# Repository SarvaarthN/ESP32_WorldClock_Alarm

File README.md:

# 12 Hr Clock

This project is a **Digital Logic Design (Sem 3) course project at VJTI**, focused on the design and implementation of a non-microcontroller-based digital clock using fundamental digital electronics components.

A **crystal oscillator** is employed to generate a stable and accurate clock signal, which is then divided and processed using a series of decade counters to achieve precise timekeeping.

The clock is configured to operate in a 12-hour format, incorporating appropriate rollover logic for hours. **Seven-segment display driver ICs** are used to interface with the displays, ensuring clear and reliable visualization of hours and minutes.

This project emphasizes a deep understanding of frequency division, time counting, sequential logic, and display interfacing, demonstrating accurate timekeeping without relying on microcontrollers or firmware, and instead leveraging core digital logic design principles.

## Folder Structure
- **Docs** – Documentation, reports, and design references  
- **PCB** – Circuit schematics, board layout, and related design files  

```12-Hr-Clock/
├── Docs/
│   └── Datasheets/
│
├── PCB/
│   ├── 12HrClock_PCB/
│   │   ├── 12HrClock_PCB-backups/
│   │   └── v1-backups/
│   │
│   └── Gerberv3/
│
└── README.md

```

## PCB Pictures

## Contributors

- [Sarvaarth Narang](https://github.com/SarvaarthN)
- [Paarth Shirsat](https://github.com/Paarth-Shirsat)
- [Bhakti Assar](https://github.com/Bhakti-A)

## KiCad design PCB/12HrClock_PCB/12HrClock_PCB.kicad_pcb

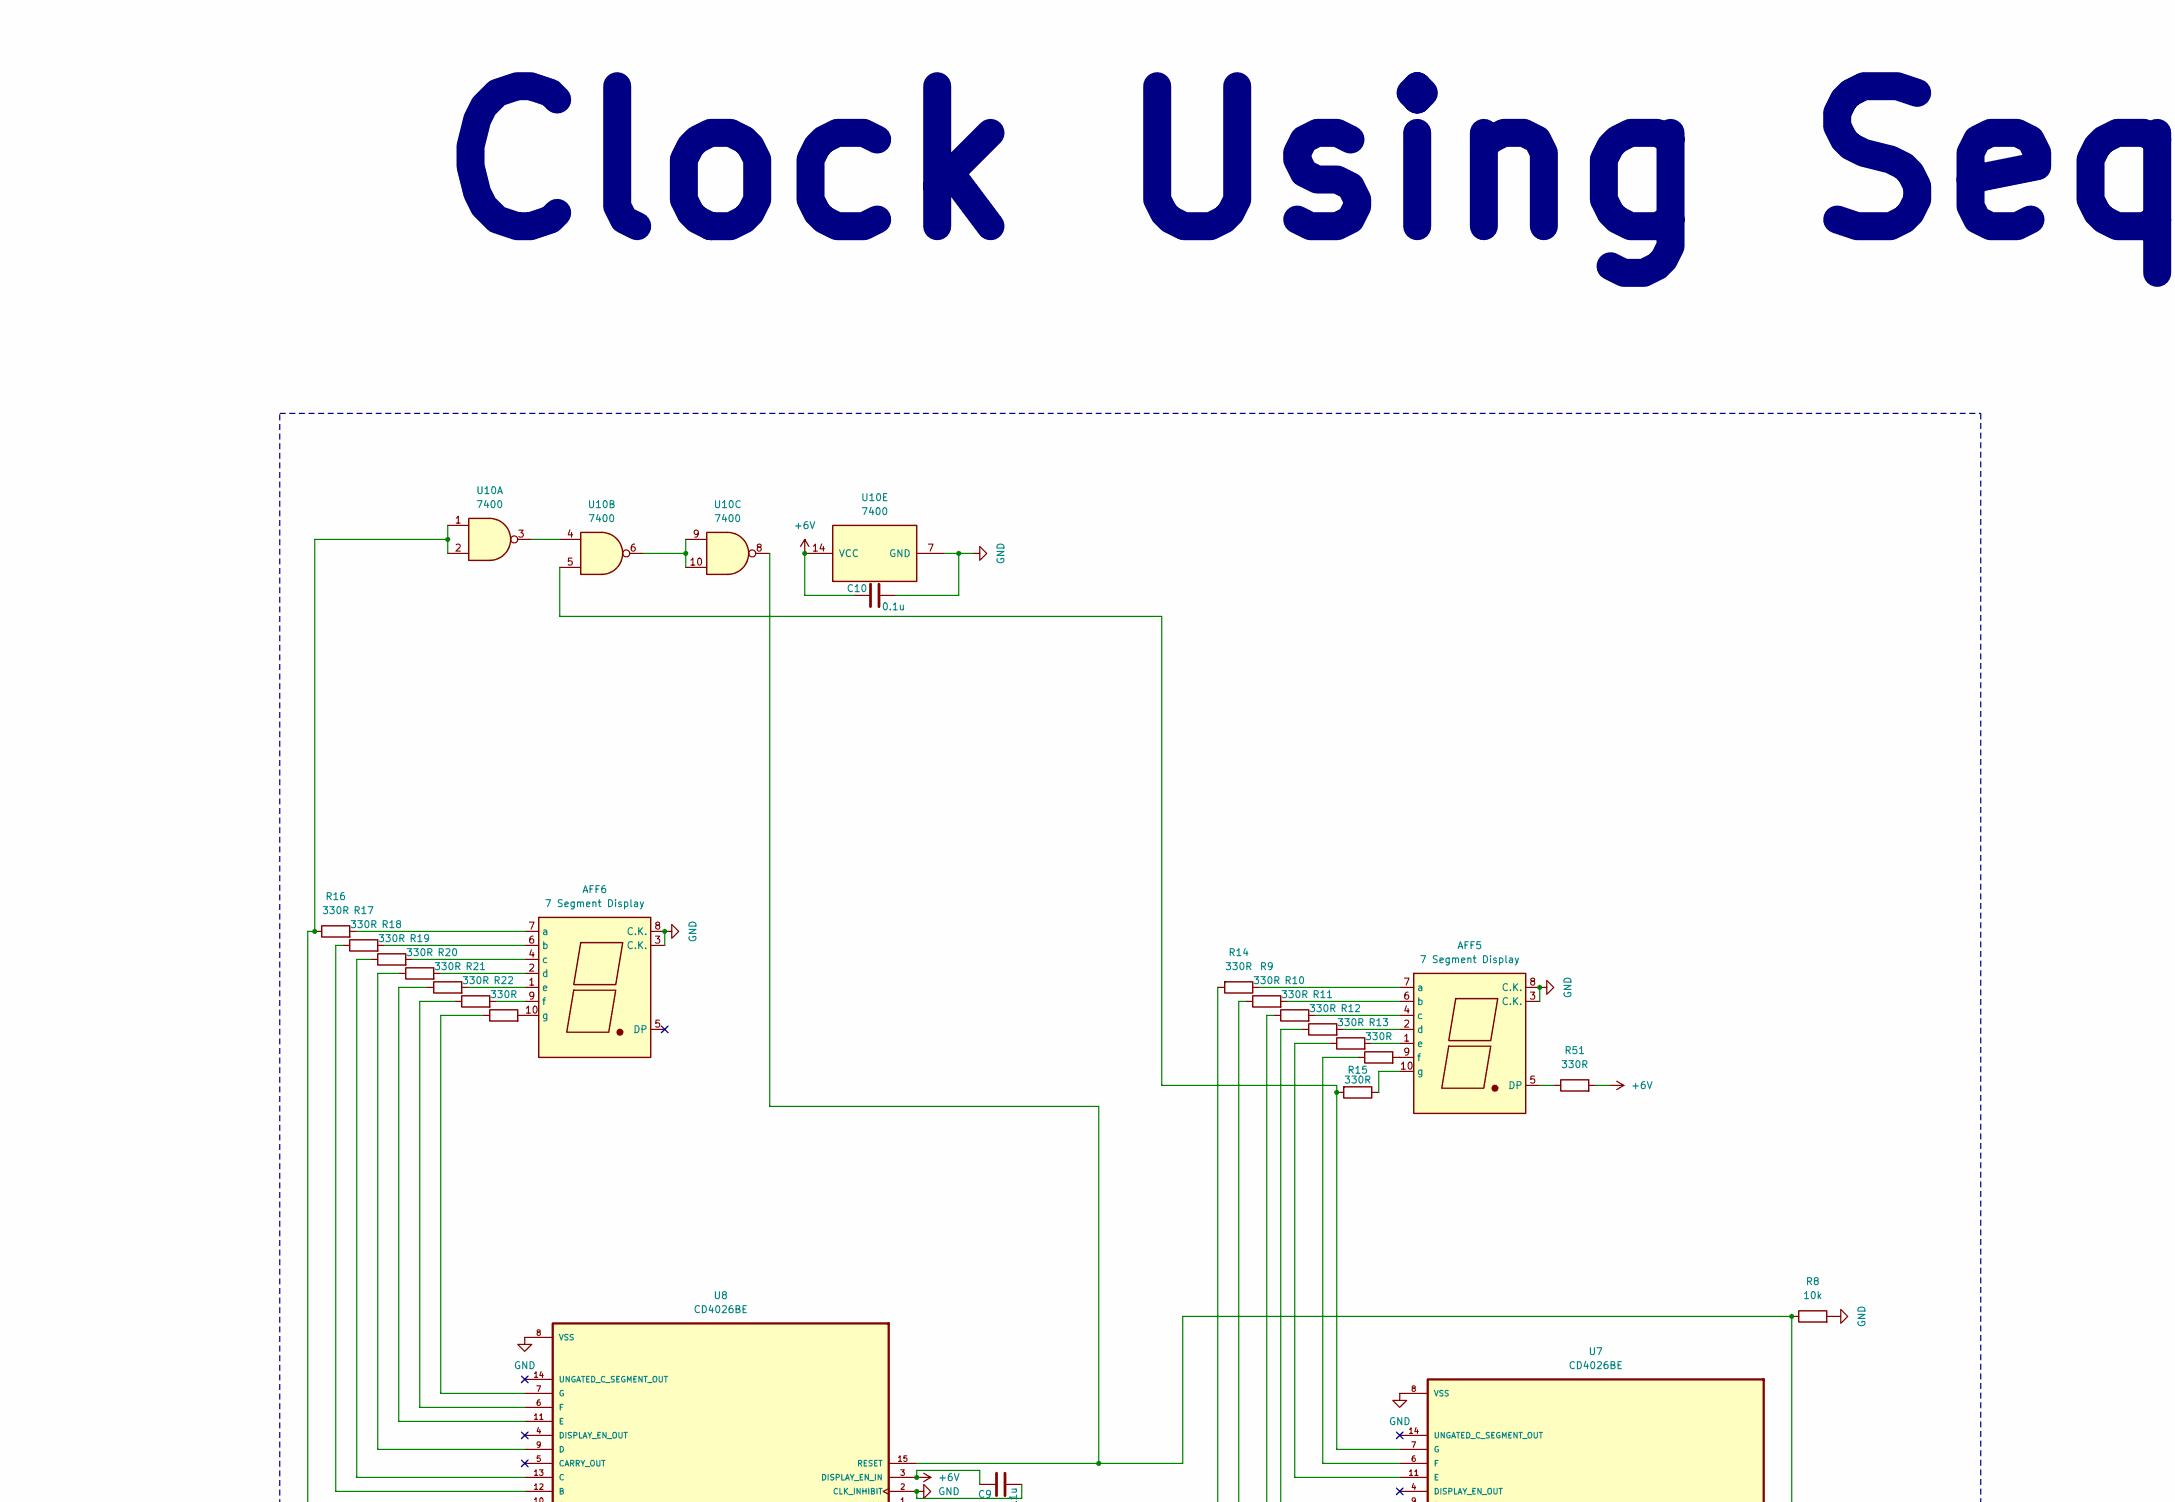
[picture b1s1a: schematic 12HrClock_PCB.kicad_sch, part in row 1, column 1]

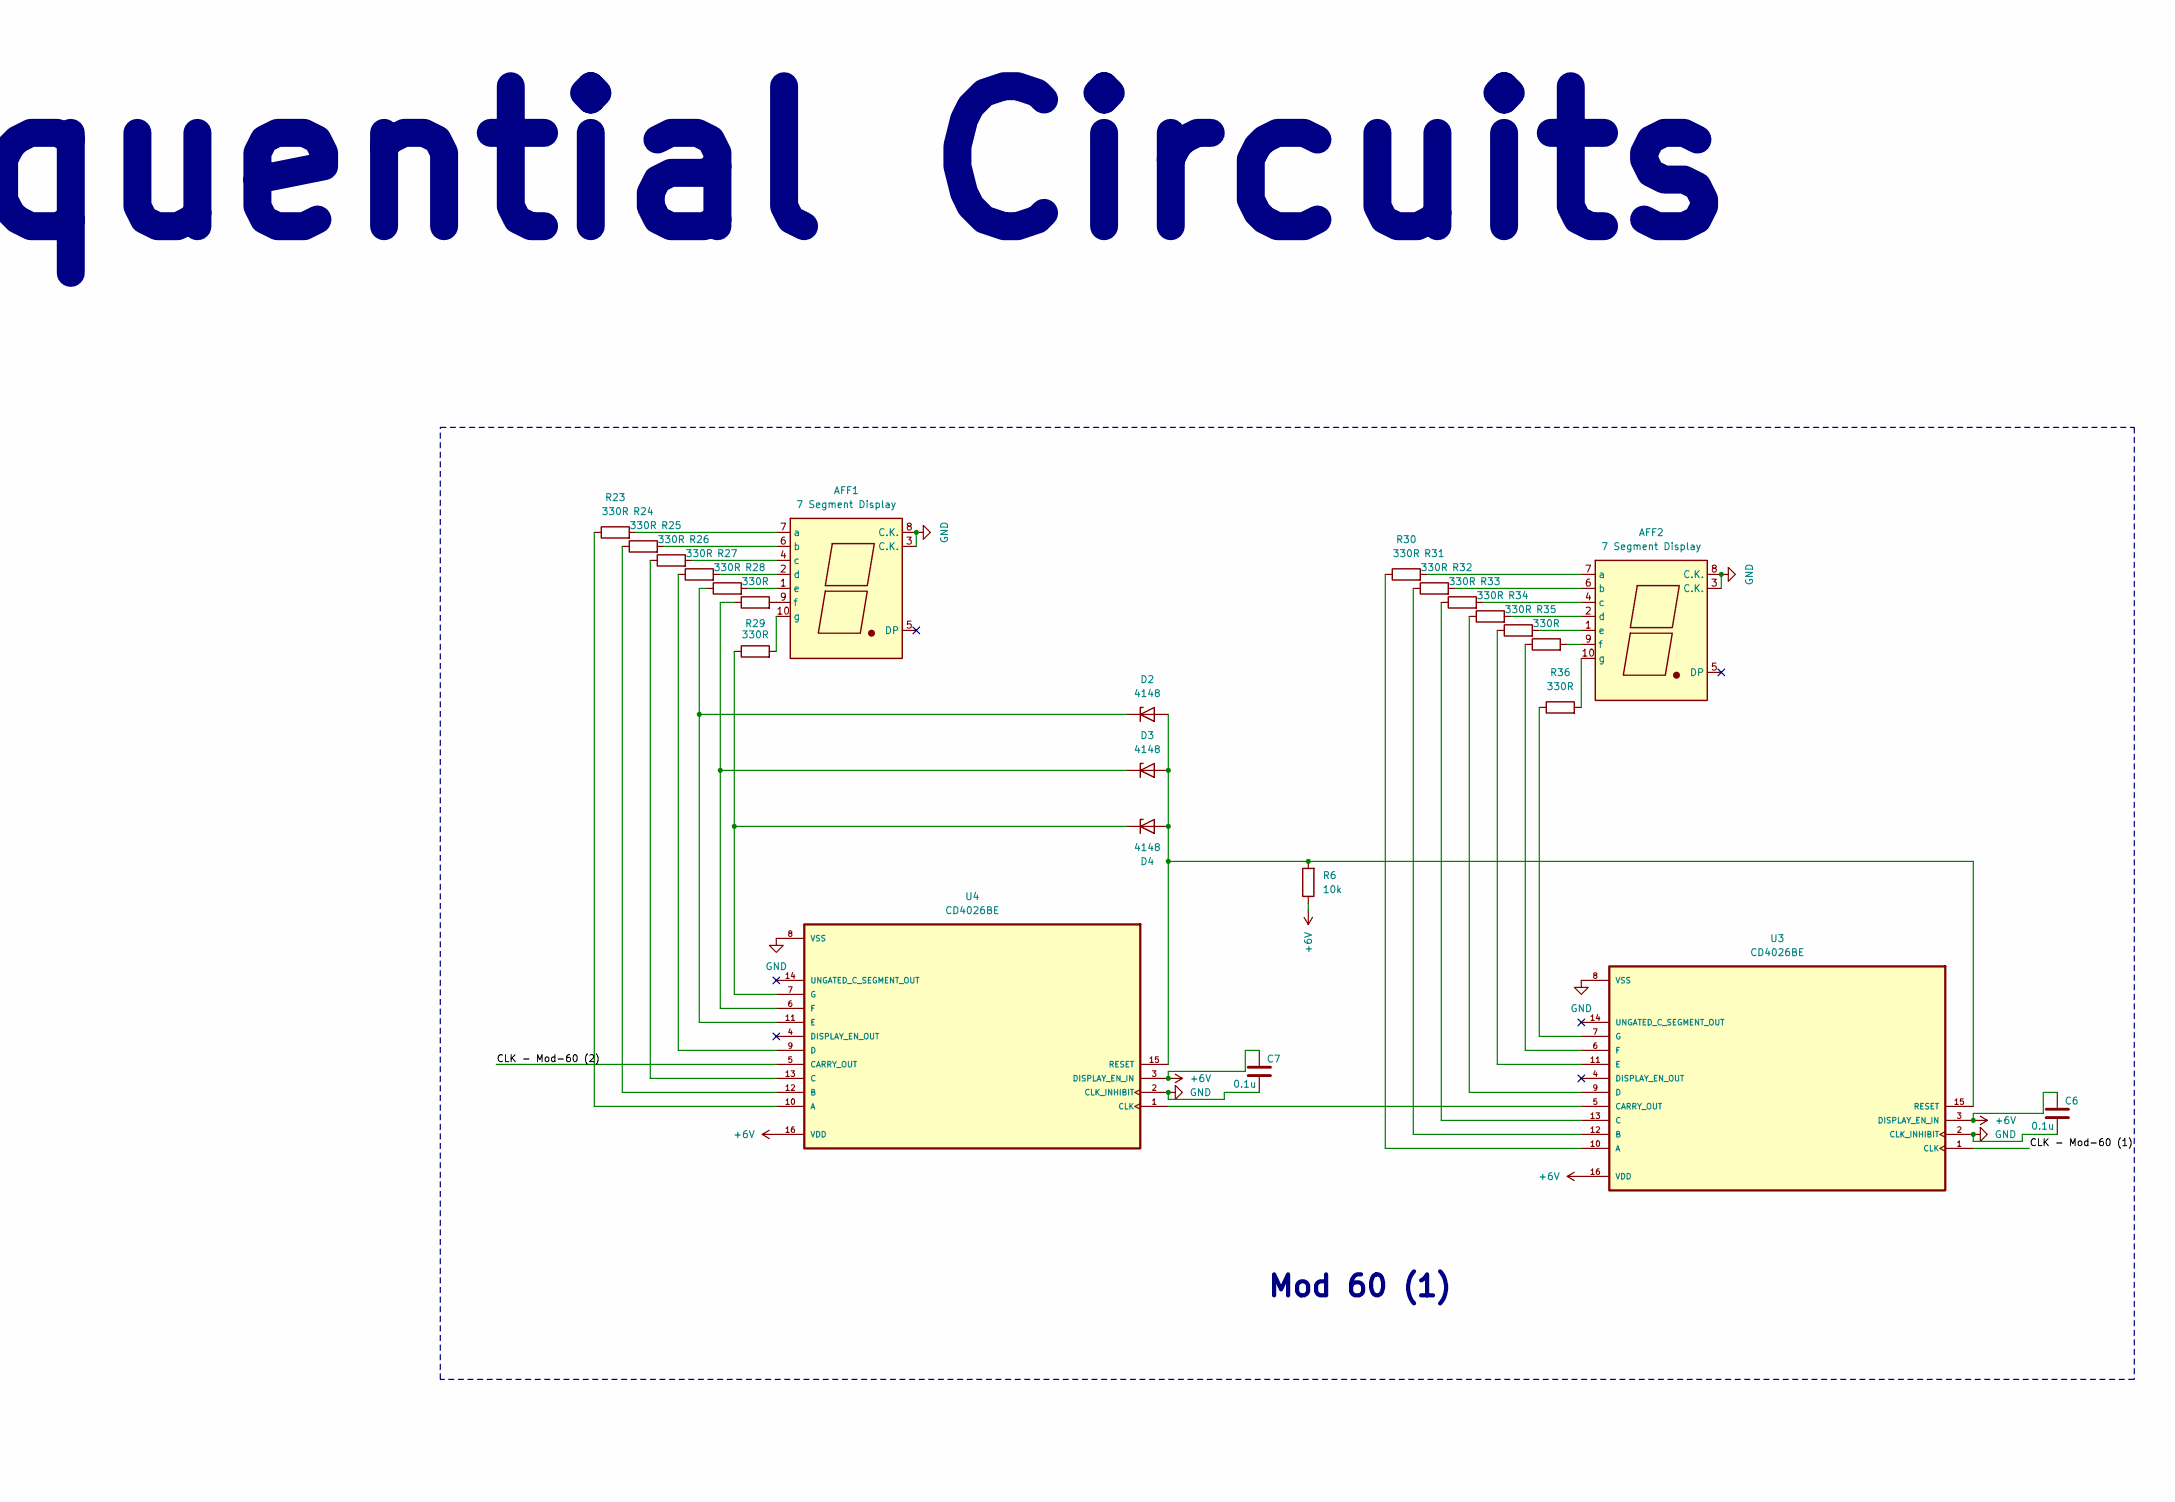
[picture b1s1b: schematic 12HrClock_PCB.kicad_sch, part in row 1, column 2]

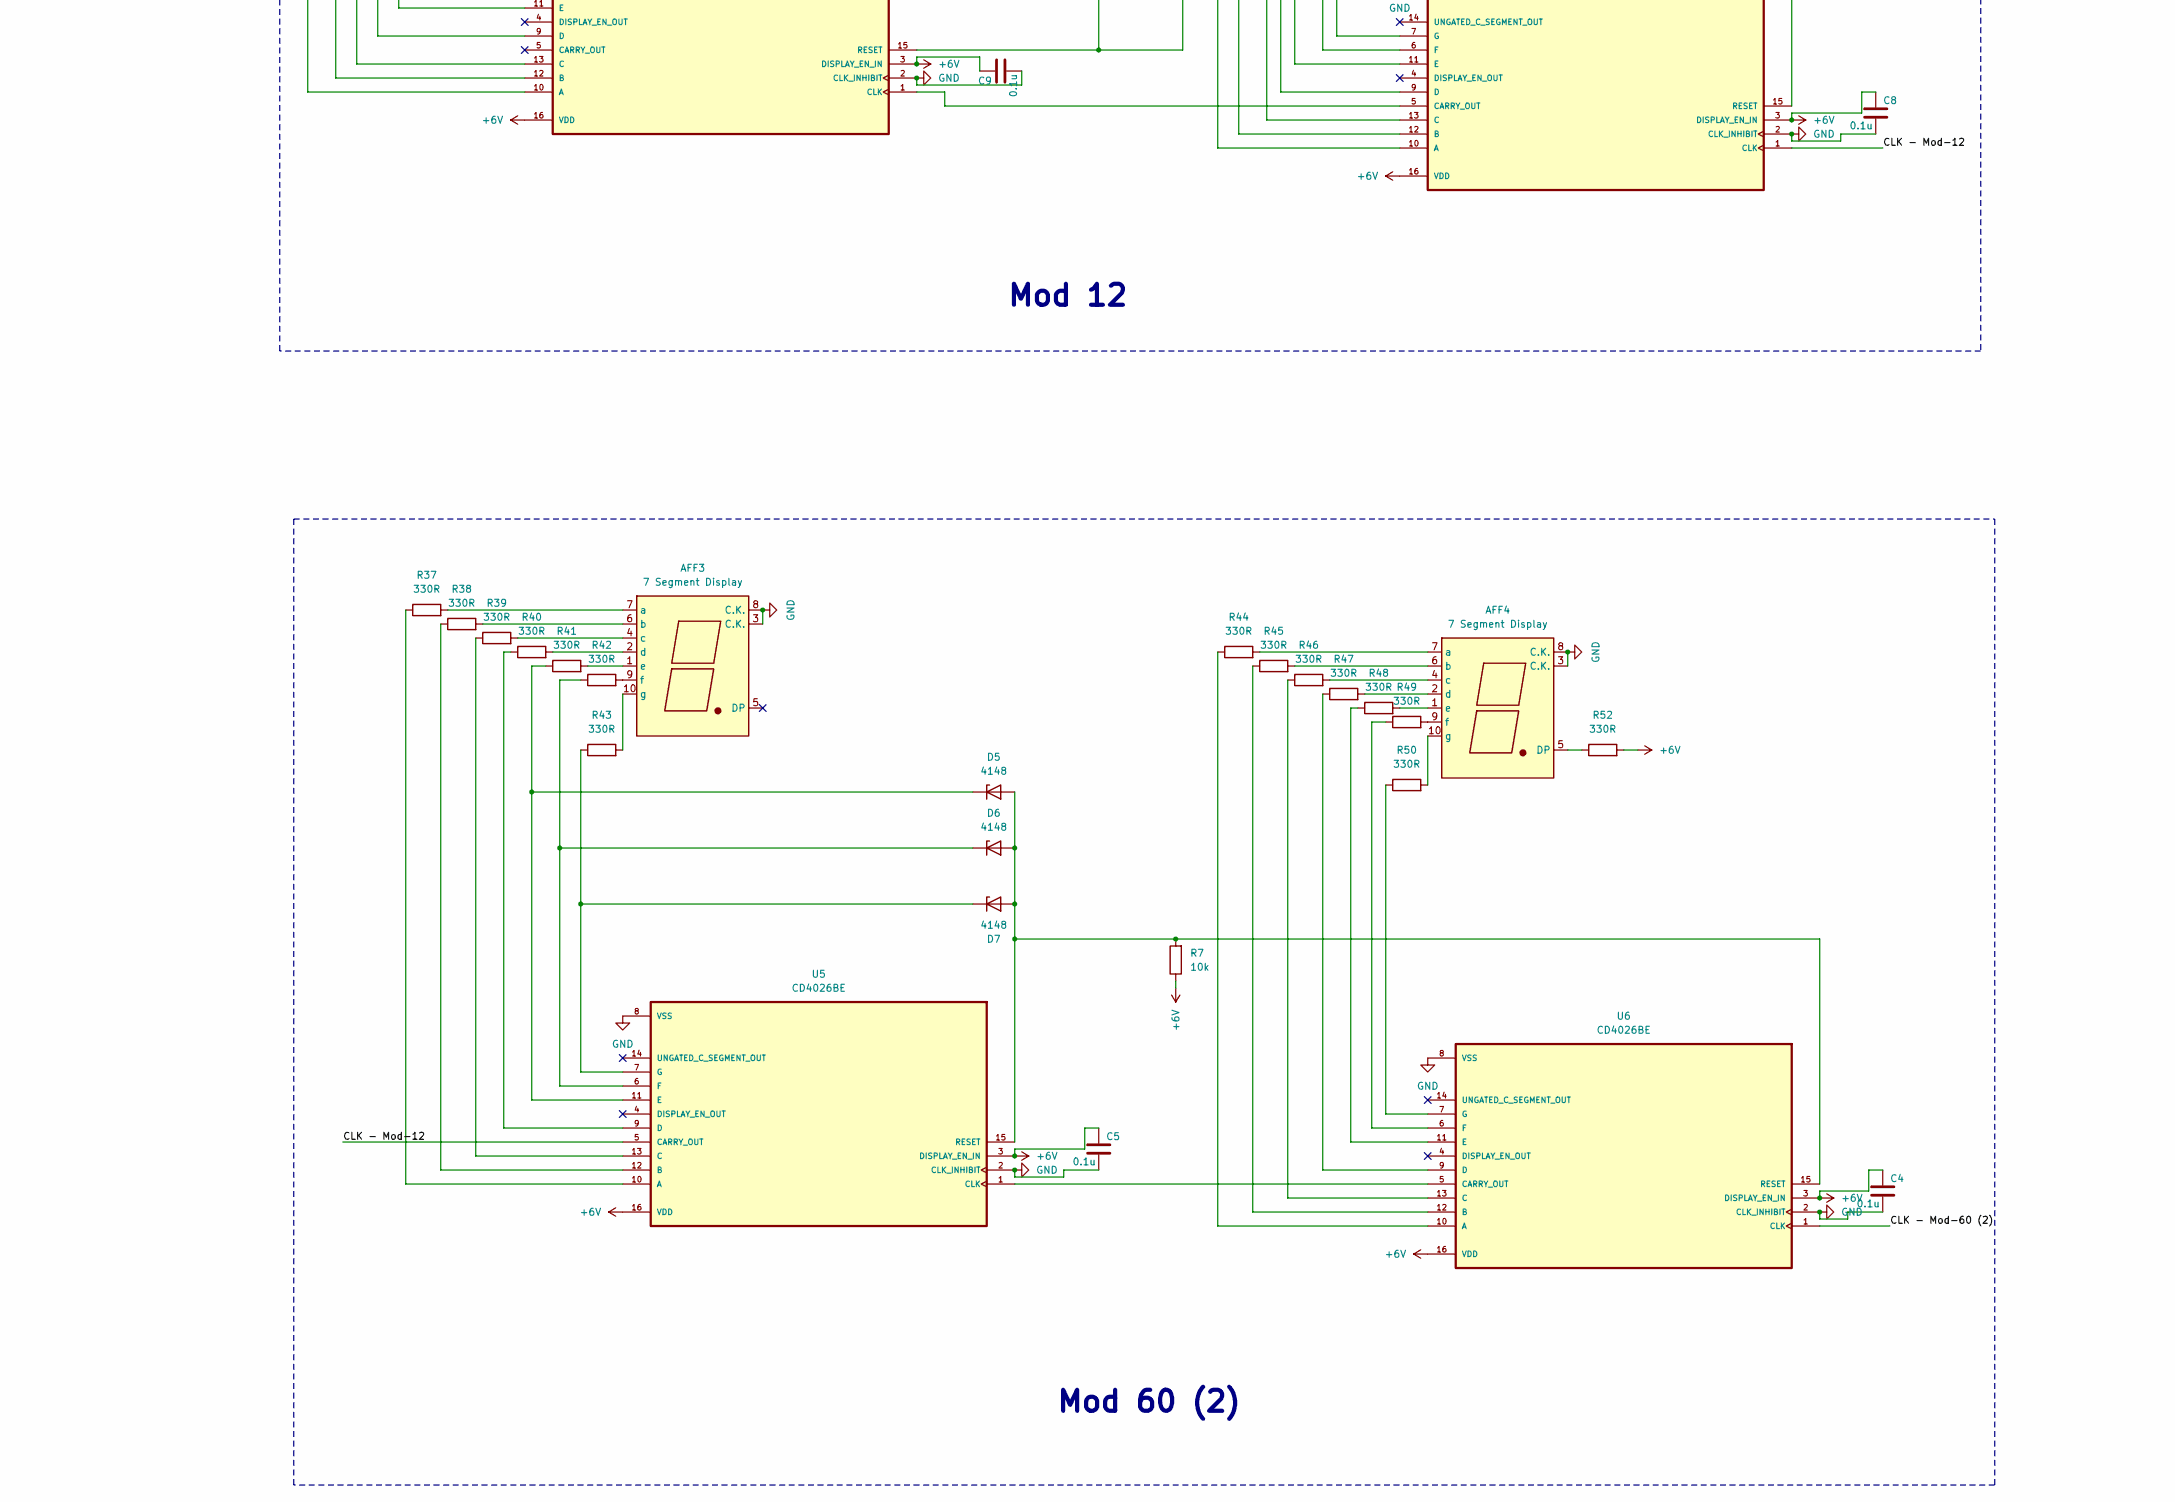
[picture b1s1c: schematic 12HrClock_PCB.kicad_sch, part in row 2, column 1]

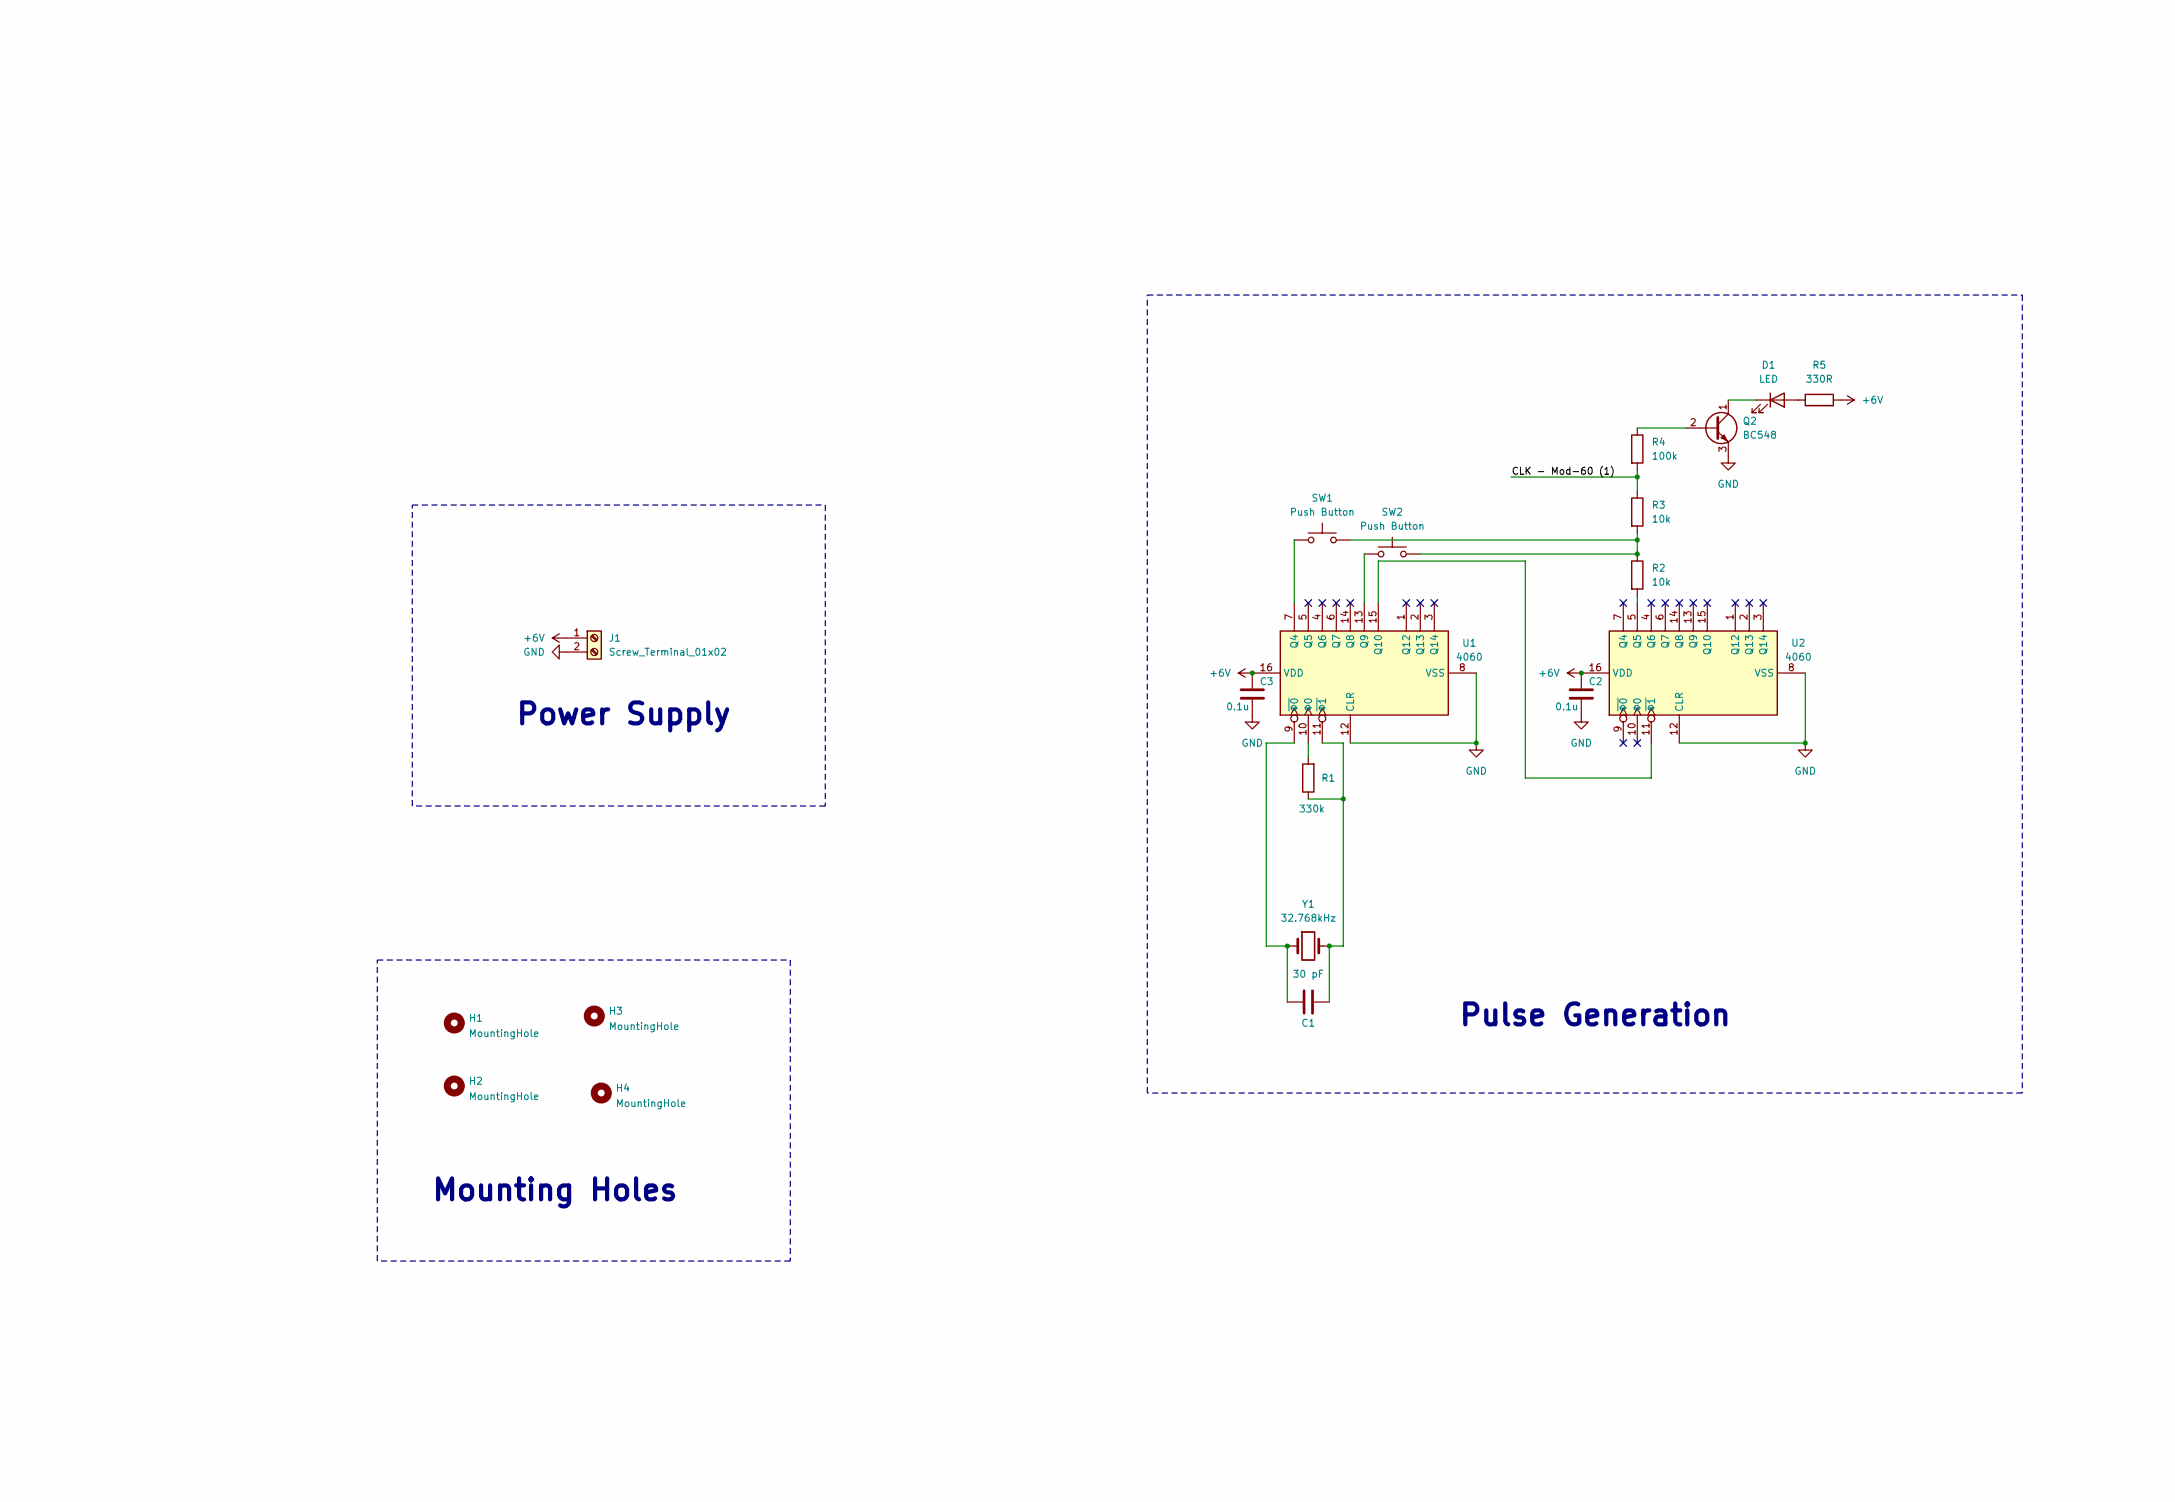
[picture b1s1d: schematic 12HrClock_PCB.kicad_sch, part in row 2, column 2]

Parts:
AFF1, AFF2, AFF3, AFF4, AFF5, AFF6: 7 Segment Display; 7SegmentLED_LTS6760_LTS6780
C1: 30 pF; C_0805_2012Metric_Pad1.18x1.45mm_HandSolder
C2, C3, C4, C5, C6, C7, C8, C9, C10: 0.1u; C_0805_2012Metric_Pad1.18x1.45mm_HandSolder
D1: LED; LED_0805_2012Metric_Pad1.15x1.40mm_HandSolder
D2, D3, D4, D5, D6, D7: 4148; D_DO-35_SOD27_P7.62mm_Horizontal
H1, H2, H3, H4: MountingHole; MountingHole_3.2mm_M3
J1: Screw_Terminal_01x02; TerminalBlock_Phoenix_PT-1,5-2-5.0-H_1x02_P5.00mm_Horizontal
Q2: BC548; TO-92_Inline
R1: 330k; R_0805_2012Metric_Pad1.20x1.40mm_HandSolder
R2, R3, R6, R7, R8: 10k; R_0805_2012Metric_Pad1.20x1.40mm_HandSolder
R4: 100k; R_0805_2012Metric_Pad1.20x1.40mm_HandSolder
R5, R9, R10, R11, R12, R13, R14, R15, R16, R17, R18, R19, R20, R21, R22, R23, R24, R25, R26, R27, R28, R29, R30, R31, R32, R33, R34, R35, R36, R37, R38, R39, R40, R41, R42, R43, R44, R45, R46, R47, R48, R49, R50, R51, R52: 330R; R_0805_2012Metric_Pad1.20x1.40mm_HandSolder
SW1, SW2: Push Button; SW_PUSH_6mm
U1, U2: 4060; DIP-16_W7.62mm_LongPads
U3, U4, U5, U6, U7, U8: CD4026BE; DIP-16_W7.62mm_LongPads
U10: 7400; DIP-14_W7.62mm_LongPads
Y1: 32.768kHz; Crystal_DS10_D1.0mm_L4.3mm_Vertical

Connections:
+6V: C2.1, C3.1, C4.1, C5.1, C6.1, C7.1, C8.1, C9.1, C10.1, J1.1, R5.2, R6.1, R7.1, R51.2, R52.2, U1.16 (VDD), U2.16 (VDD), U3.3 (DISPLAY_EN_IN), U3.16 (VDD), U4.3 (DISPLAY_EN_IN), U4.16 (VDD), U5.3 (DISPLAY_EN_IN), U5.16 (VDD), U6.3 (DISPLAY_EN_IN), U6.16 (VDD), U7.3 (DISPLAY_EN_IN), U7.16 (VDD), U8.3 (DISPLAY_EN_IN), U8.16 (VDD), U10.14 (VCC)
/CLK - Mod-12: U5.5 (CARRY_OUT), U7.1 (CLK)
/CLK - Mod-60 (1): R3.1, R4.2, U3.1 (CLK)
/CLK - Mod-60 (2): U4.5 (CARRY_OUT), U6.1 (CLK)
GND: AFF1.3 (C.K.), AFF1.8 (C.K.), AFF2.3 (C.K.), AFF2.8 (C.K.), AFF3.3 (C.K.), AFF3.8 (C.K.), AFF4.3 (C.K.), AFF4.8 (C.K.), AFF5.3 (C.K.), AFF5.8 (C.K.), AFF6.3 (C.K.), AFF6.8 (C.K.), C2.2, C3.2, C4.2, C5.2, C6.2, C7.2, C8.2, C9.2, C10.2, J1.2, Q2.3 (E), R8.2, U1.8 (VSS), U1.12 (CLR), U2.8 (VSS), U2.12 (CLR), U3.2 (CLK_INHIBIT), U3.8 (VSS), U4.2 (CLK_INHIBIT), U4.8 (VSS), U5.2 (CLK_INHIBIT), U5.8 (VSS), U6.2 (CLK_INHIBIT), U6.8 (VSS), U7.2 (CLK_INHIBIT), U7.8 (VSS), U8.2 (CLK_INHIBIT), U8.8 (VSS), U10.7 (GND)
unnamed: AFF1.7 (a), R23.2
unnamed: AFF1.6 (b), R24.2
unnamed: AFF1.4 (c), R25.2
unnamed: AFF1.2 (d), R26.2
unnamed: AFF1.1 (e), R27.2
unnamed: AFF1.9 (f), R28.2
unnamed: AFF1.10 (g), R29.2
unnamed: AFF2.7 (a), R30.2
unnamed: AFF2.6 (b), R31.2
unnamed: AFF2.4 (c), R32.2
unnamed: AFF2.2 (d), R33.2
unnamed: AFF2.1 (e), R34.2
unnamed: AFF2.9 (f), R35.2
unnamed: AFF2.10 (g), R36.2
unnamed: AFF3.7 (a), R37.2
unnamed: AFF3.6 (b), R38.2
unnamed: AFF3.4 (c), R39.2
unnamed: AFF3.2 (d), R40.2
unnamed: AFF3.1 (e), R41.2
unnamed: AFF3.9 (f), R42.2
unnamed: AFF3.10 (g), R43.2
unnamed: AFF4.5 (DP), R52.1
unnamed: AFF4.7 (a), R44.2
unnamed: AFF4.6 (b), R45.2
unnamed: AFF4.4 (c), R46.2
unnamed: AFF4.2 (d), R47.2
unnamed: AFF4.1 (e), R48.2
unnamed: AFF4.9 (f), R49.2
unnamed: AFF4.10 (g), R50.2
unnamed: AFF5.5 (DP), R51.1
unnamed: AFF5.7 (a), R14.1
unnamed: AFF5.6 (b), R9.2
unnamed: AFF5.4 (c), R10.2
unnamed: AFF5.2 (d), R11.2
unnamed: AFF5.1 (e), R12.2
unnamed: AFF5.9 (f), R13.2
unnamed: AFF5.10 (g), R15.1
unnamed: AFF6.7 (a), R16.2
unnamed: AFF6.6 (b), R17.2
unnamed: AFF6.4 (c), R18.2
unnamed: AFF6.2 (d), R19.2
unnamed: AFF6.1 (e), R20.2
unnamed: AFF6.9 (f), R21.2
unnamed: AFF6.10 (g), R22.2
unnamed: D1.2 (A), R5.1
unnamed: D1.1 (K), Q2.1 (C)
unnamed: D2.2 (A), D3.2 (A), D4.2 (A), R6.2, U3.15 (RESET), U4.15 (RESET)
unnamed: D2.1 (K), R27.1, U4.11 (E)
unnamed: D3.1 (K), R28.1, U4.6 (F)
unnamed: D4.1 (K), R29.1, U4.7 (G)
unnamed: D5.2 (A), D6.2 (A), D7.2 (A), R7.2, U5.15 (RESET), U6.15 (RESET)
unnamed: D5.1 (K), R41.1, U5.11 (E)
unnamed: D6.1 (K), R42.1, U5.6 (F)
unnamed: D7.1 (K), R43.1, U5.7 (G)
unnamed: Q2.2 (B), R4.1
unnamed: R2.1, R3.2, SW1.2, SW2.2
unnamed: SW1.1, U1.7 (Q4)
unnamed: SW2.1, U1.13 (Q9)
unnamed: U1.15 (Q10), U2.11 (~Φ1)
unnamed: C1.1, U1.9 (~Φ0), Y1.1
unnamed: C1.2, R1.1, U1.11 (~Φ1), Y1.2
unnamed: R1.2, U1.10 (Φ0)
unnamed: R2.2, U2.5 (Q5)
unnamed: R30.1, U3.10 (A)
unnamed: R31.1, U3.12 (B)
unnamed: R32.1, U3.13 (C)
unnamed: U3.5 (CARRY_OUT), U4.1 (CLK)
unnamed: R33.1, U3.9 (D)
unnamed: R34.1, U3.11 (E)
unnamed: R35.1, U3.6 (F)
unnamed: R36.1, U3.7 (G)
unnamed: R23.1, U4.10 (A)
unnamed: R24.1, U4.12 (B)
unnamed: R25.1, U4.13 (C)
unnamed: R26.1, U4.9 (D)
unnamed: R37.1, U5.10 (A)
unnamed: R38.1, U5.12 (B)
unnamed: R39.1, U5.13 (C)
unnamed: U5.1 (CLK), U6.5 (CARRY_OUT)
unnamed: R40.1, U5.9 (D)
unnamed: R44.1, U6.10 (A)
unnamed: R45.1, U6.12 (B)
unnamed: R46.1, U6.13 (C)
unnamed: R47.1, U6.9 (D)
unnamed: R48.1, U6.11 (E)
unnamed: R49.1, U6.6 (F)
unnamed: R50.1, U6.7 (G)
unnamed: R14.2, U7.10 (A)
unnamed: R9.1, U7.12 (B)
unnamed: R10.1, U7.13 (C)
unnamed: U7.5 (CARRY_OUT), U8.1 (CLK)
unnamed: R11.1, U7.9 (D)
unnamed: R12.1, U7.11 (E)
unnamed: R13.1, U7.6 (F)
unnamed: R15.2, U7.7 (G), U10.5
unnamed: R8.1, U7.15 (RESET), U8.15 (RESET), U10.8
unnamed: R16.1, U8.10 (A), U10.1, U10.2
unnamed: R17.1, U8.12 (B)
unnamed: R18.1, U8.13 (C)
unnamed: R19.1, U8.9 (D)
unnamed: R20.1, U8.11 (E)
unnamed: R21.1, U8.6 (F)
unnamed: R22.1, U8.7 (G)
unnamed: U10.3, U10.4
unnamed: U10.6, U10.9, U10.10

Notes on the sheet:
Pulse Generation
Mod 60 (1)
Power Supply
Mounting Holes
Clock Using Sequential Circuits
Mod 60 (2)
Mod 12

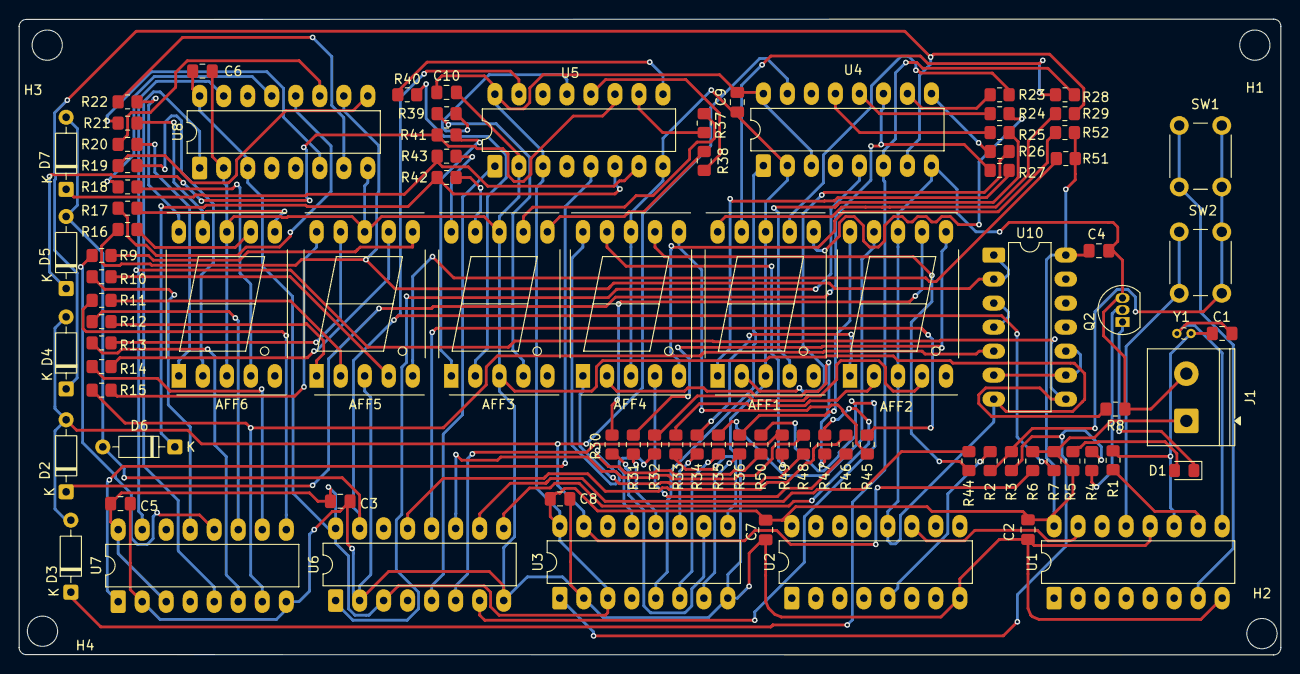
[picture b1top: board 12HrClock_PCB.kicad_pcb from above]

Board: 2 copper layers, 133.5 x 67.2 mm, 93 parts (0 on the bottom side), 110 nets.

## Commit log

2025-10-03 initial commit 2
2025-10-03 initial commit 3
2025-10-04 Added Schematic and footprints
2025-10-19 Updated PCB Schematics
2025-10-20 Updated Schematic, made PCB Design
2025-10-28 Updated Schematic
2025-11-03 PCB routed V5
2025-11-04 PCB Routing In progress
2025-11-06 Solved PCB Errors
2025-11-06 Minor Readme fixes
2025-11-06 Added Mounted Holes and Logos
2025-11-07 Final Changes Made
2026-01-28 Fixed Project Documentatation
2026-01-28 Upgraded Documentation
